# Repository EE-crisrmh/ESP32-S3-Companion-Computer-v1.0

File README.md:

# ESP32-S3-DevBoard-v1.0

## Overview
This project is the first version of my **ESP32-S3**. The purpose of this board is to act as a **wireless communication, expansion, and development support board**.

This board is intended to handle **higher-level support functions** such as wireless communication, sensor interfacing, debugging, and future peripheral expansion.

This is **Version 1.0**, meaning the primary goal was to design and lay out a functional first revision that establishes the core architecture for future integration and testing.

---

## Project Goals
The main goals of this board were to:

- Build a **modular companion board** for a future platforms
- Create a hardware platform around the **ESP32-S3**
- Add support for **wireless communication and external peripherals**
- Provide **easy bring-up, programming, and debugging access**
- Establish a foundation for future onboard communication, telemetry, and sensor expansion

---

## Current Features

### Core Hardware
- **ESP32-S3 WiFi module**
- **4-layer PCB design**
- **USB-C power input**
- **LM1117DT-3.3V LDO regulator**
- **ESP-PROG compatible programming/debug header**

### User / Bring-Up Features
- **BOOT switch**
- **RESET switch**
- **USER switch**
- **RGB LEDs**
- **Green power LED**

### Sensor / Expansion Features
- **SI7021-GMR temperature and humidity sensor** on the **I2C bus**
- **QWIIC connector** for external I2C peripherals
- **2x5 SPI expansion header**
  - planned for future peripherals such as a **W5500 Ethernet module**

### Mechanical
- **3.2 mm mounting holes**

---

## PCB Stack-Up
This board was designed as a **4-layer PCB** to improve routing flexibility, grounding, and power distribution.

### Stack-Up
- **Top Layer**
- **0.196 mm prepreg**
- **Inner Layer 1**
- **1.03 mm core**
- **Inner Layer 2**
- **0.196 mm prepreg**
- **Bottom Layer**

This stack-up was chosen to provide a better structure for embedded routing compared to a simpler 2-layer design.

---

## Why I Built This
I wanted to start building the electronics architecture for my own **autonomous drone system** rather than only working with off-the-shelf development boards.

This board is one of the first major hardware building blocks in that process.

The idea is to split the system into multiple roles:

- **STM32 board** → real-time flight control / lower-level control tasks
- **ESP32-S3 companion board** → communication, expansion, debugging, and support functions

This gives me a cleaner system architecture and more flexibility as the project grows.

## Design Focus for v1.0
For Version 1.0, the focus was on:

- Building a clean first-pass board architecture
- Integrating the core ESP32-S3 support hardware
- Adding modular expansion interfaces
- Making firmware flashing and bring-up easier
- Creating a platform that can be improved in future revisions

This version is primarily about getting the **hardware foundation** in place.

---

## Future Plans
This board is still in its early stages, and future revisions will likely include both electrical and firmware improvements.

### Planned Next Steps
- Order and assemble the first revision of the board
- Perform initial bring-up and power validation
- Verify USB-C power and 3.3V regulation
- Test programming/debug functionality with ESP-PROG
- Bring up onboard LEDs, switches, and sensor interfaces
- Validate I2C and SPI expansion functionality

### Long-Term Plans
- Pair this board with a **custom STM32 flight controller**
- Use it as part of a full **autonomous drone electronics stack**
- Add communication between the ESP32-S3 and STM32
- Expand support for telemetry and external peripherals
- Potentially integrate Ethernet or other network-capable modules for development and testing
- Continue revising the board based on testing and system needs

---

## Version
**Current Version:** `v1.0`

This is the first revision of the board and is intended to serve as the initial hardware foundation for future testing and iteration.

---

## Author
Designed and developed by me as part of my long-term embedded systems / autonomous drone project.

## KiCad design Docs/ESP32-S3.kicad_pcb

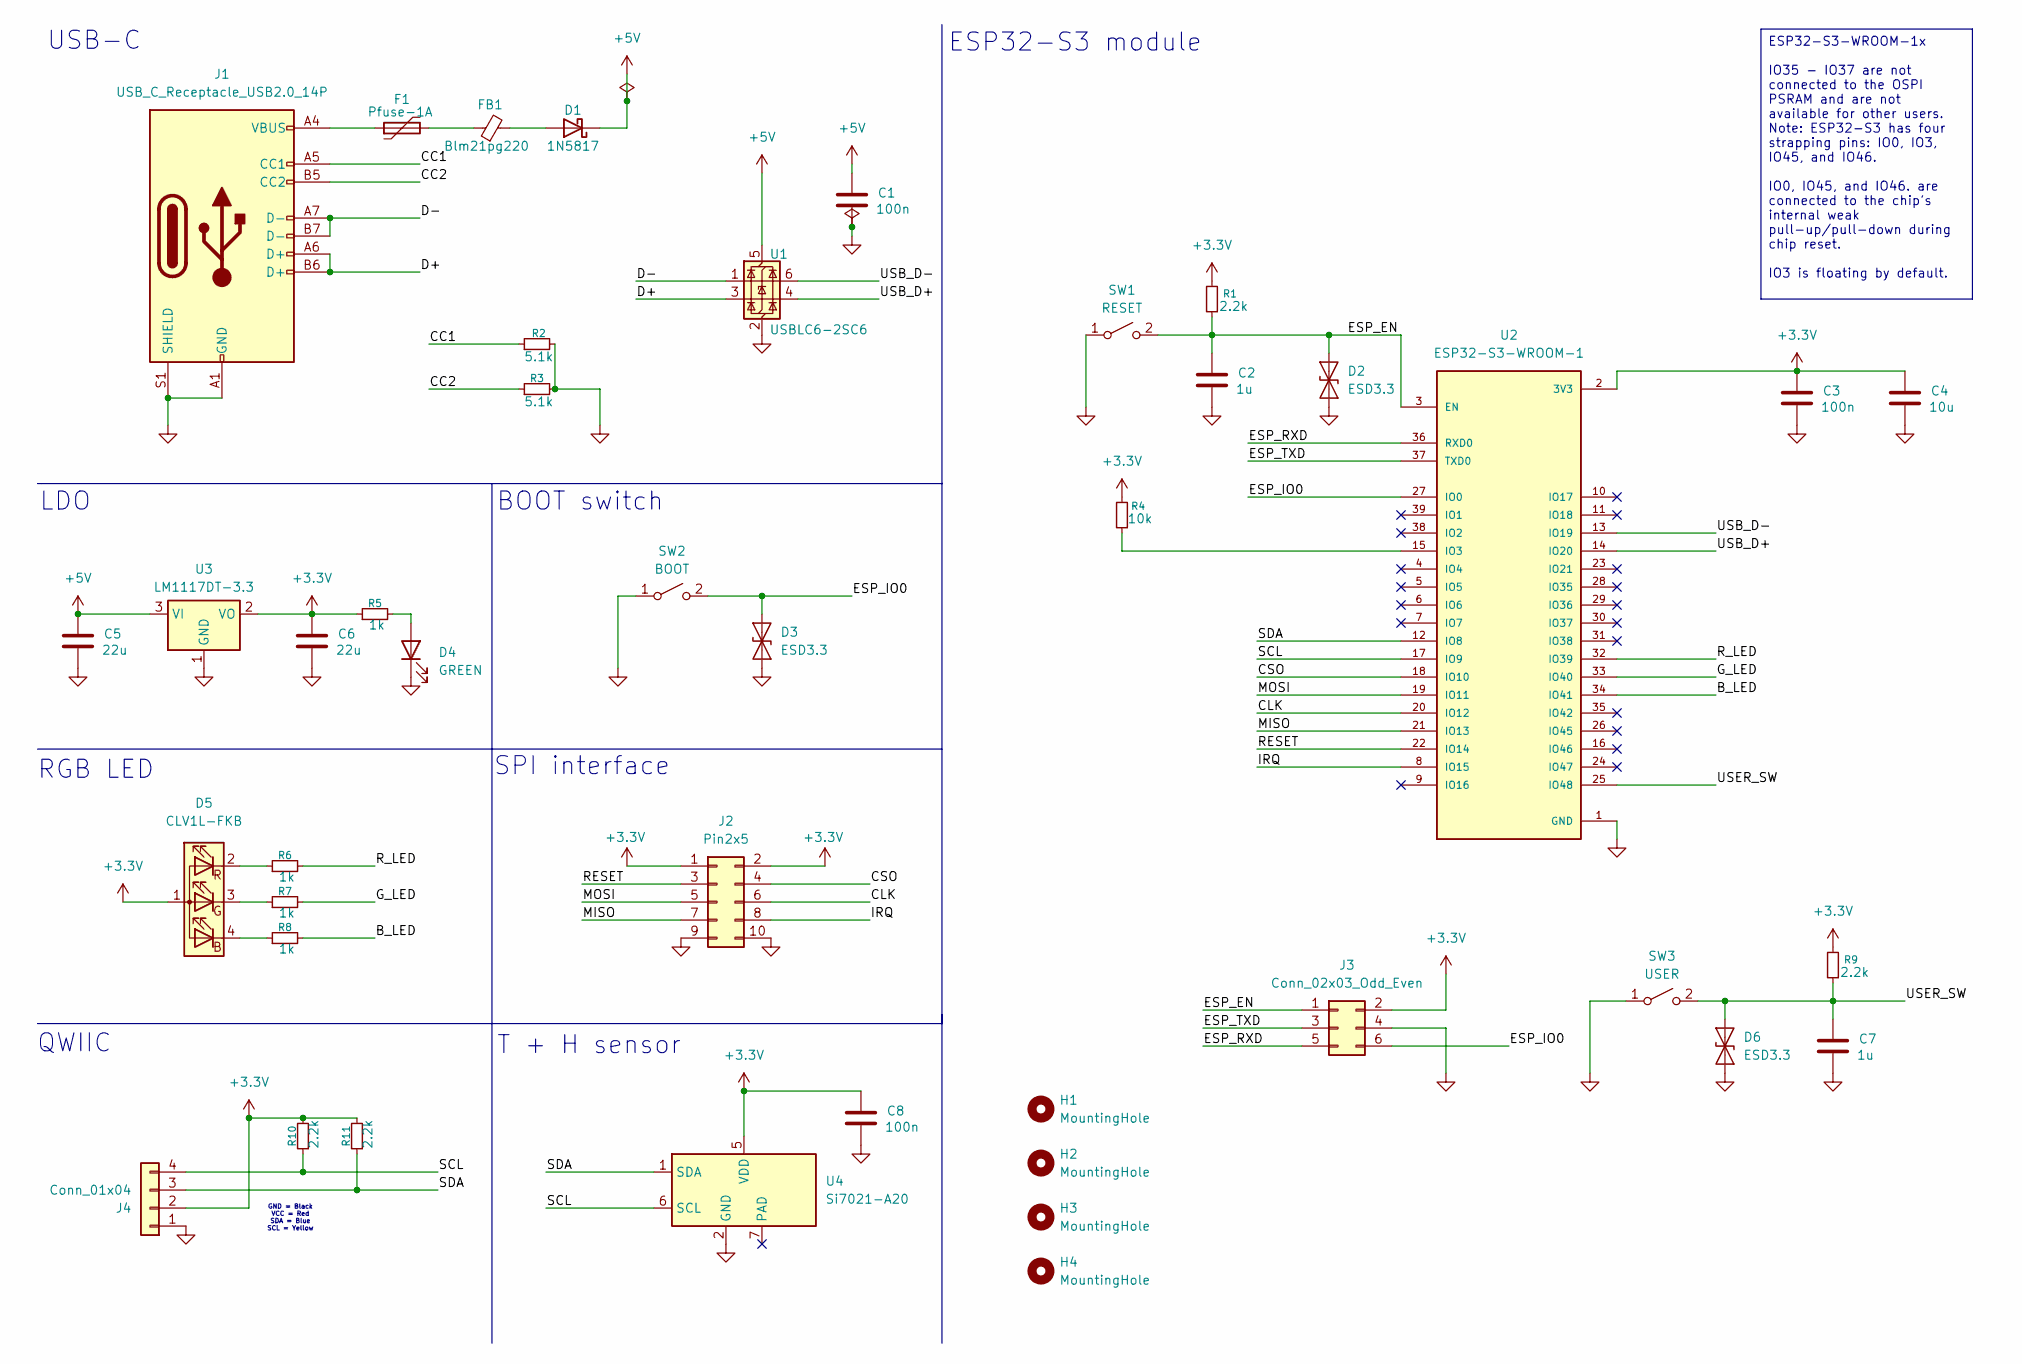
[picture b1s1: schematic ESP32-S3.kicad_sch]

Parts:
C1, C3, C8: 100n; C_0402_1005Metric
C2, C7: 1u; C_0603_1608Metric
C4: 10u; C_0603_1608Metric
C5, C6: 22u; C_0805_2012Metric
D1: 1N5817; D_DO-41_SOD81_P7.62mm_Horizontal
D2, D3, D6: ESD3.3; D_SOD-923
D4: GREEN; LED_0805_2012Metric
D5: CLV1L-FKB; LED_Cree-PLCC4_3.2x2.8mm_CCW
F1: Pfuse-1A; D_1206_3216Metric
FB1: Blm21pg220; L_0805_2012Metric
H1, H2, H3, H4: MountingHole; MountingHole_3.2mm_M3
J1: USB_C_Receptacle_USB2.0_14P; USB_C_Receptacle_HRO_TYPE-C-31-M-12
J2: Pin2x5; PinHeader_2x05_P2.54mm_Vertical
J3: Conn_02x03_Odd_Even; PinHeader_2x03_P2.54mm_Vertical
J4: Conn_01x04; JST_SH_SM04B-SRSS-TB_1x04-1MP_P1.00mm_Horizontal
R1, R9, R10, R11: 2.2k; R_0402_1005Metric
R2, R3: 5.1k; R_0402_1005Metric
R4: 10k; R_0402_1005Metric
R5, R6, R7, R8: 1k; R_0805_2012Metric
SW1: RESET; SW_SPST_B3U-1000P
SW2: BOOT; SW_SPST_B3U-1000P
SW3: USER; SW_Tactile_SPST_Angled_PTS645Vx39-2LFS
U1: USBLC6-2SC6; SOT-23-6
U2: ESP32-S3-WROOM-1; PARTREV v1.0
U3: LM1117DT-3.3; TO-252-3_TabPin2
U4: Si7021-A20; DFN-6-1EP_3x3mm_P1mm_EP1.5x2.4mm

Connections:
+3.3V: C3.1, C4.1, C6.1, C8.1, D5.1 (A), J2.1, J2.2, J3.2, J4.2, R1.2, R4.2, R5.1, R9.2, R10.2, R11.2, U2.2 (3V3), U3.2 (VO), U4.5 (VDD)
+5V: C1.1, C5.1, D1.1 (K), U1.5 (VBUS), U3.3 (VI)
/B_LED: R8.2, U2.34 (IO41)
/CC1: J1.A5 (CC1), R2.1; also elsewhere on the board
/CC2: J1.B5 (CC2), R3.1; also elsewhere on the board
/CLK: J2.6, U2.20 (IO12)
/CSO: J2.4, U2.18 (IO10)
/D+: J1.A6 (D+), J1.B6 (D+), U1.3 (I/O2); also elsewhere on the board
/D-: J1.A7 (D-), J1.B7 (D-), U1.1 (I/O1); also elsewhere on the board
/ESP_EN: C2.1, D2.2 (A2), J3.1, R1.1, SW1.2 (B), U2.3 (EN)
/ESP_IO0: D3.2 (A2), J3.6, SW2.2 (B), U2.27 (IO0)
/ESP_RXD: J3.5, U2.36 (RXD0)
/ESP_TXD: J3.3, U2.37 (TXD0)
/G_LED: R7.2, U2.33 (IO40)
/IRQ: J2.8, U2.8 (IO15)
/MISO: J2.7, U2.21 (IO13)
/MOSI: J2.5, U2.19 (IO11)
/RESET: J2.3, U2.22 (IO14)
/R_LED: R6.2, U2.32 (IO39)
/SCL: J4.4, R10.1, U2.17 (IO9), U4.6 (SCL)
/SDA: J4.3, R11.1, U2.12 (IO8), U4.1 (SDA)
/USB_D+: U1.4 (I/O2), U2.14 (IO20)
/USB_D-: U1.6 (I/O1), U2.13 (IO19)
/USER_SW: C7.1, D6.2 (A2), R9.1, SW3.2 (B), U2.25 (IO48); also elsewhere on the board
GND: C1.2, C2.2, C3.2, C4.2, C5.2, C6.2, C7.2, C8.2, D2.1 (A1), D3.1 (A1), D4.1 (K), D6.1 (A1), J1.A1 (GND), J1.A12 (GND), J1.B1 (GND), J1.B12 (GND), J1.S1 (SHIELD), J2.9, J2.10, J3.4, J4.1, R2.2, R3.2, SW1.1 (A), SW2.1 (A), SW3.1 (A), U1.2 (GND), U2.1 (GND), U2.40 (GND), U2.41_1 (GND), U2.41_2 (GND), U2.41_3 (GND), U2.41_4 (GND), U2.41_5 (GND), U2.41_6 (GND), U2.41_7 (GND), U2.41_8 (GND), U2.41_9 (GND), U3.1 (GND), U4.2 (GND); also elsewhere on the board
unnamed: D1.2 (A), FB1.2
unnamed: D4.2 (A), R5.2
unnamed: D5.4 (BK), R8.1
unnamed: D5.3 (GK), R7.1
unnamed: D5.2 (RK), R6.1
unnamed 30: F1.1, J1.A4 (VBUS), J1.A9 (VBUS), J1.B4 (VBUS), J1.B9 (VBUS); also elsewhere on the board
unnamed: F1.2, FB1.1
unnamed: R4.1, U2.15 (IO3)

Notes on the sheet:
GND = Black VCC = Red SDA = Blue SCL = Yellow
ESP32-S3 module
USB-C
RGB LED
BOOT switch
QWIIC
T + H sensor
LDO
SPI interface
ESP32-S3-WROOM-1x IO35 - IO37 are not connected to the OSPI PSRAM and are not available for other users. Note: ESP32-S3 has four strapping pins: IO0, IO3, IO45, and IO46. IO0, IO45, and IO46. are connected to the chip's internal weak pull-up/pull-down during chip reset. IO3 is floating by default.

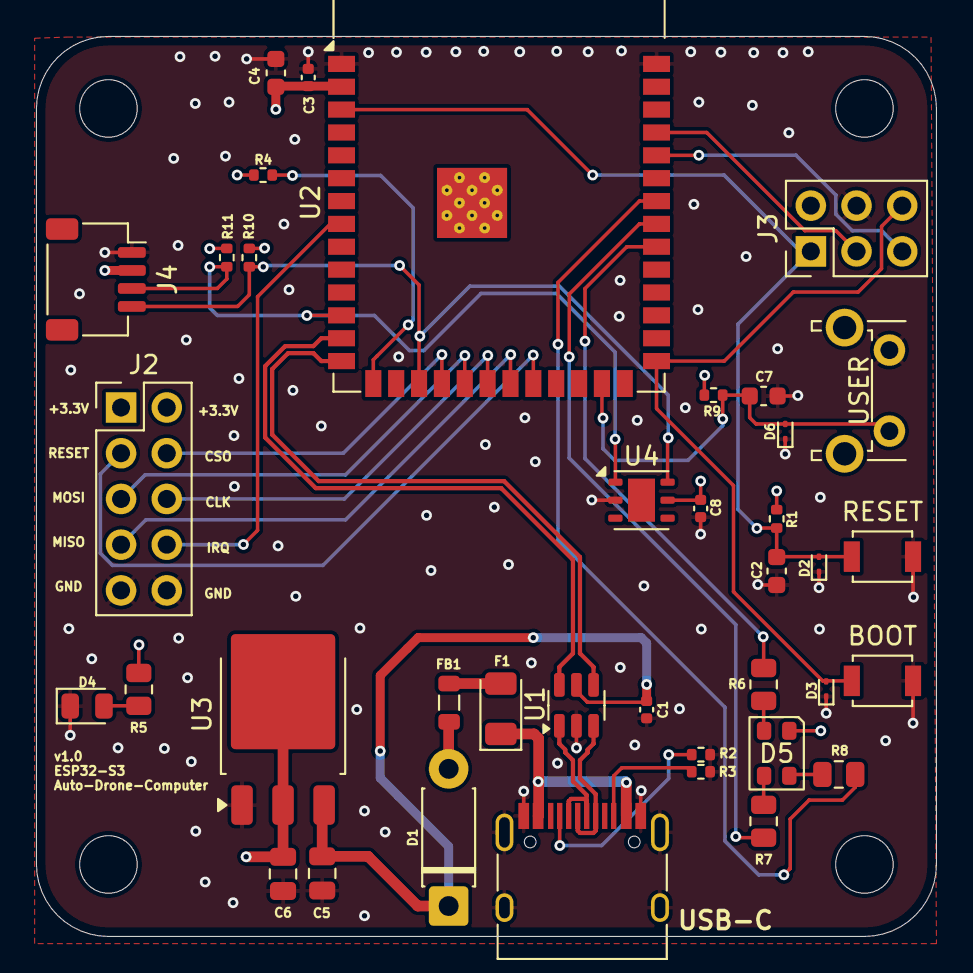
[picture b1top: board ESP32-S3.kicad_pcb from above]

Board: 4 copper layers, 50.0 x 50.0 mm, 42 parts (0 on the bottom side), 33 nets.

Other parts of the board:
USB-C: USB_C_Receptacle_USB2.0_14P; USB_C_Receptacle_HRO_TYPE-C-31-M-12
USER: USER; SW_Tactile_SPST_Angled_PTS645Vx39-2LFS

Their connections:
/CC1: USB-C.A5 (CC1); also elsewhere on the board
/CC2: USB-C.B5 (CC2); also elsewhere on the board
/D+: USB-C.A6 (D+), USB-C.B6 (D+); also elsewhere on the board
/D-: USB-C.A7 (D-), USB-C.B7 (D-); also elsewhere on the board
/USER_SW: USER.2 (B); also elsewhere on the board
GND: USB-C.A1 (GND), USB-C.A12 (GND), USB-C.B1 (GND), USB-C.B12 (GND), USB-C.S1 (SHIELD), USER.1 (A); also elsewhere on the board
unnamed 30: USB-C.A4 (VBUS), USB-C.A9 (VBUS), USB-C.B4 (VBUS), USB-C.B9 (VBUS); also elsewhere on the board

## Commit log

2026-03-28 Create Schematic
